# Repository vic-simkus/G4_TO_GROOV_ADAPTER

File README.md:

# G4 TO GROOV ADAPTER
## Motivation
I found out, after purchasing a pile of gear, that the G4 output modules mounted in a G4PB24 would not work with a GRV-ODCSRC-24.  Reason being that the GRV-ODCSRC-24 is a "sourcing" module, while the G4PB24 expects a "sinking" module.  

While this could have been better documented by OPTO 22, it is what is it and I needed to be able to used the G4PB24 for my project.  Nothing else would do for various reasons.

Hence this project.  The project is an adapter board with a 50 pin ribbon connector on one end and a spring loaded terminal on the other end.  The design is super simple - it's 24 NPN transistors.

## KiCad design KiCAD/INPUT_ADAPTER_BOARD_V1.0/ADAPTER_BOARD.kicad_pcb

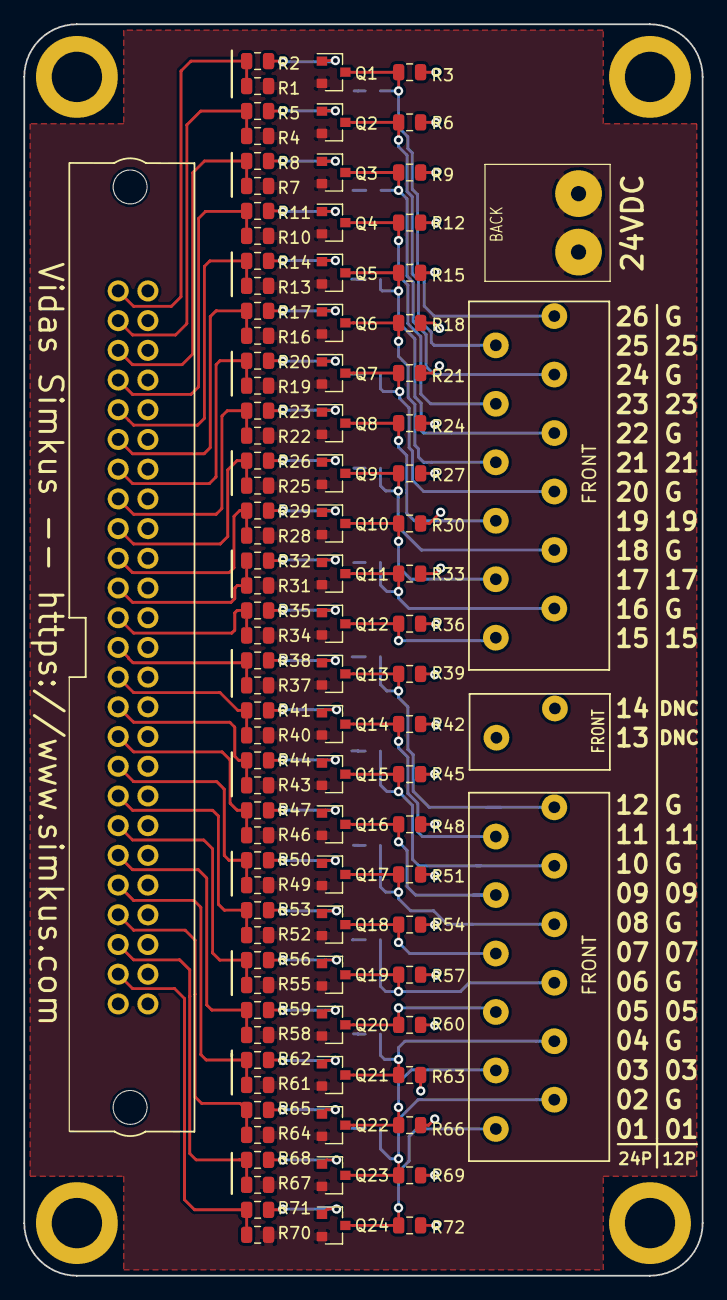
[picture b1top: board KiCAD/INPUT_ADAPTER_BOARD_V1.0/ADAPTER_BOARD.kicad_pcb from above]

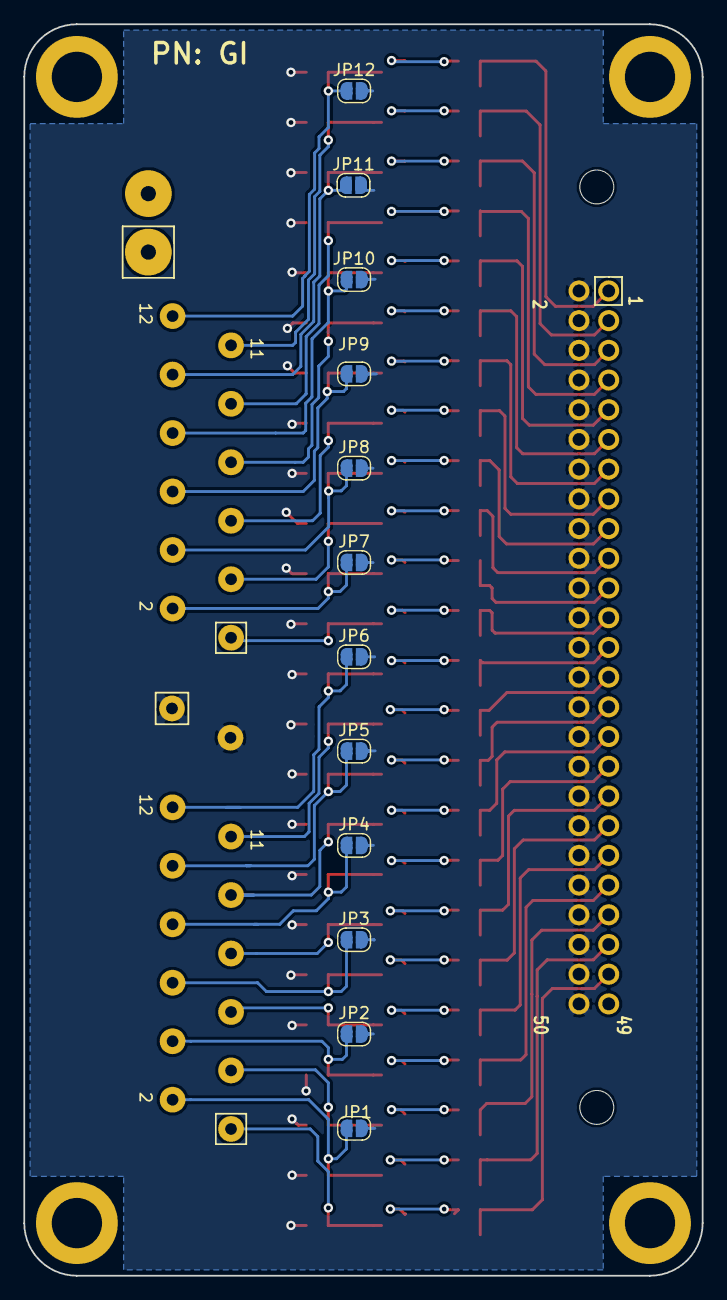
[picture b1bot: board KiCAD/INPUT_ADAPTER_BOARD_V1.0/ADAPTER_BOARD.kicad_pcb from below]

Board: 2 copper layers, 58.0 x 107.0 mm, 113 parts (12 on the bottom side), 74 nets.

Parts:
BOARD1: Conn_02x25_Odd_Even; FCI_50PIN
JP1, JP2, JP3, JP4, JP5, JP6, JP7, JP8, JP9, JP10, JP11, JP12: 12P; SolderJumper-2_P1.3mm_Open_RoundedPad1.0x1.5mm
PLC1: Conn_01x02; 2_POS_SPRING_TERM
PLC1-2, PLC13-2: Conn_01x12; 12_POS_SPRING_TERM
Q1, Q2, Q3, Q4, Q5, Q6, Q7, Q8, Q9, Q10, Q11, Q12, Q13, Q14, Q15, Q16, Q17, Q18, Q19, Q20, Q21, Q22, Q23, Q24: Q_NPN_CBE; SOT-23
R1, R2, R3, R4, R5, R6, R7, R8, R9, R10, R11, R12, R13, R14, R15, R16, R17, R18, R19, R20, R21, R22, R23, R24, R25, R26, R27, R28, R29, R30, R31, R32, R33, R34, R35, R36, R37, R38, R39, R40, R41, R42, R43, R44, R45, R46, R47, R48, R49, R50, R51, R52, R53, R54, R55, R56, R57, R58, R59, R60, R61, R62, R63, R64, R65, R66, R67, R68, R69, R70, R71, R72: 10K; R_0805_2012Metric
VDC1: Conn_01x02; 2_POS_SCREW_TERM

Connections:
24VDC: Q1.2, Q2.2, Q3.2, Q4.2, Q5.2, Q6.2, Q7.2, Q8.2, Q9.2, Q10.2, Q11.2, Q12.2, Q13.2, Q14.2, Q15.2, Q16.2, Q17.2, Q18.2, Q19.2, Q20.2, Q21.2, Q22.2, Q23.2, Q24.2, R1.2, R4.2, R7.2, R10.2, R13.2, R16.2, R19.2, R22.2, R25.2, R28.2, R31.2, R34.2, R37.2, R40.2, R43.2, R46.2, R49.2, R52.2, R55.2, R58.2, R61.2, R64.2, R67.2, R70.2, VDC1.1, VDC1.2
/B01: BOARD1.1, R1.1, R2.2
/B02: BOARD1.3, R4.1, R5.2
/B03: BOARD1.5, R7.1, R8.2
/B04: BOARD1.7, R10.1, R11.2
/B05: BOARD1.9, R13.1, R14.2
/B06: BOARD1.11, R16.1, R17.2
/B07: BOARD1.13, R19.1, R20.2
/B08: BOARD1.15, R22.1, R23.2
/B09: BOARD1.17, R25.1, R26.2
/B10: BOARD1.19, R28.1, R29.2
/B11: BOARD1.21, R31.1, R32.2
/B12: BOARD1.23, R34.1, R35.2
/B13: BOARD1.25, R37.1, R38.2
/B14: BOARD1.27, R40.1, R41.2
/B15: BOARD1.29, R43.1, R44.2
/B16: BOARD1.31, R46.1, R47.2
/B17: BOARD1.33, R49.1, R50.2
/B18: BOARD1.35, R52.1, R53.2
/B19: BOARD1.37, R55.1, R56.2
/B20: BOARD1.39, R58.1, R59.2
/B21: BOARD1.41, R61.1, R62.2
/B22: BOARD1.43, R64.1, R65.2
/B23: BOARD1.45, R67.1, R68.2
/B24: BOARD1.47, R70.1, R71.2
/P01: JP12.1, PLC1-2.12, Q1.3, R3.2
/P02: PLC1-2.11, Q2.3, R6.2
/P03: JP11.1, PLC1-2.10, Q3.3, R9.2
/P04: PLC1-2.9, Q4.3, R12.2
/P05: JP10.1, PLC1-2.8, Q5.3, R15.2
/P06: PLC1-2.7, Q6.3, R18.2
/P07: JP9.1, PLC1-2.6, Q7.3, R21.2
/P08: PLC1-2.5, Q8.3, R24.2
/P09: JP8.1, PLC1-2.4, Q9.3, R27.2
/P10: PLC1-2.3, Q10.3, R30.2
/P11: JP7.1, PLC1-2.2, Q11.3, R33.2
/P12: PLC1-2.1, Q12.3, R36.2
/P13: JP6.1, PLC13-2.12, Q13.3, R39.2
/P14: PLC13-2.11, Q14.3, R42.2
/P15: JP5.1, PLC13-2.10, Q15.3, R45.2
/P16: PLC13-2.9, Q16.3, R48.2
/P17: JP4.1, PLC13-2.8, Q17.3, R51.2
/P18: PLC13-2.7, Q18.3, R54.2
/P19: JP3.1, PLC13-2.6, Q19.3, R57.2
/P20: PLC13-2.5, Q20.3, R60.2
/P21: JP2.1, PLC13-2.4, Q21.3, R63.2
/P22: PLC13-2.3, Q22.3, R66.2
/P23: JP1.1, PLC13-2.2, Q23.3, R69.2
/P24: PLC13-2.1, Q24.3, R72.2
GND: BOARD1.2, BOARD1.4, BOARD1.6, BOARD1.8, BOARD1.10, BOARD1.12, BOARD1.14, BOARD1.16, BOARD1.18, BOARD1.20, BOARD1.22, BOARD1.24, BOARD1.26, BOARD1.28, BOARD1.30, BOARD1.32, BOARD1.34, BOARD1.36, BOARD1.38, BOARD1.40, BOARD1.42, BOARD1.44, BOARD1.46, BOARD1.48, BOARD1.50, JP1.2, JP2.2, JP3.2, JP4.2, JP5.2, JP6.2, JP7.2, JP8.2, JP9.2, JP10.2, JP11.2, JP12.2, PLC1.1, PLC1.2, R3.1, R6.1, R9.1, R12.1, R15.1, R18.1, R21.1, R24.1, R27.1, R30.1, R33.1, R36.1, R39.1, R42.1, R45.1, R48.1, R51.1, R54.1, R57.1, R60.1, R63.1, R66.1, R69.1, R72.1
unnamed: Q1.1, R2.1
unnamed: Q2.1, R5.1
unnamed: Q3.1, R8.1
unnamed: Q4.1, R11.1
unnamed: Q5.1, R14.1
unnamed: Q6.1, R17.1
unnamed: Q7.1, R20.1
unnamed: Q8.1, R23.1
unnamed: Q9.1, R26.1
unnamed: Q10.1, R29.1
unnamed: Q11.1, R32.1
unnamed: Q12.1, R35.1
unnamed: Q13.1, R38.1
unnamed: Q14.1, R41.1
unnamed: Q15.1, R44.1
unnamed: Q16.1, R47.1
unnamed: Q17.1, R50.1
unnamed: Q18.1, R53.1
unnamed: Q19.1, R56.1
unnamed: Q20.1, R59.1
unnamed: Q21.1, R62.1
unnamed: Q22.1, R65.1
unnamed: Q23.1, R68.1
unnamed: Q24.1, R71.1

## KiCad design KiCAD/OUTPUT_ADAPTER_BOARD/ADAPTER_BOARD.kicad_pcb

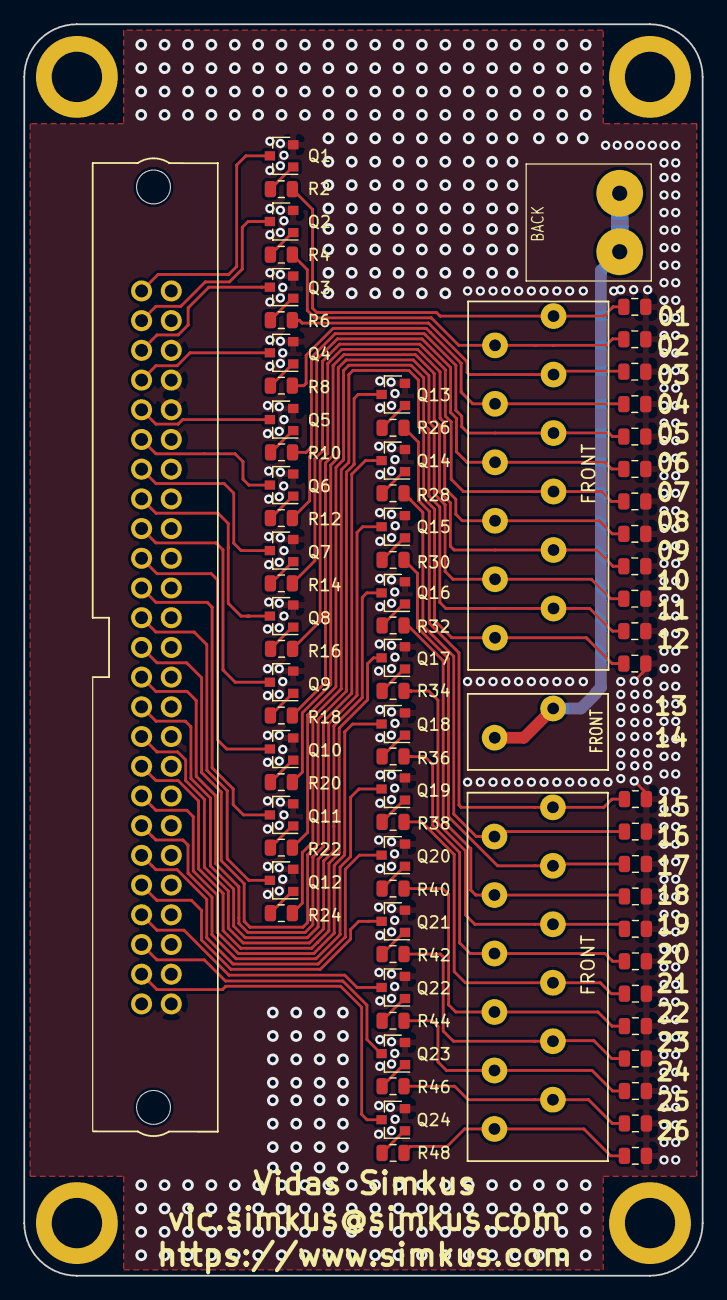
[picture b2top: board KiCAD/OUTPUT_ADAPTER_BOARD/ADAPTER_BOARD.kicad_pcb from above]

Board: 2 copper layers, 58.0 x 107.0 mm, 77 parts (0 on the bottom side), 74 nets.

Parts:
BOARD1: Conn_02x25_Odd_Even; FCI_50PIN
PLC1-12, PLC13-14: Conn_01x12; 12_POS_SPRING_TERM
PLC24: Conn_01x02; 2_POS_SPRING_TERM
Q1, Q2, Q3, Q4, Q5, Q6, Q7, Q8, Q9, Q10, Q11, Q12, Q13, Q14, Q15, Q16, Q17, Q18, Q19, Q20, Q21, Q22, Q23, Q24: Q_NPN_CBE; SOT-23
R1, R3, R5, R7, R9, R11, R13, R15, R17, R19, R21, R23, R25, R27, R29, R31, R33, R35, R37, R39, R41, R43, R45, R47: 10K; R_0805_2012Metric
R2, R4, R6, R8, R10, R12, R14, R16, R18, R20, R22, R24, R26, R28, R30, R32, R34, R36, R38, R40, R42, R44, R46, R48: 2K2; R_0805_2012Metric
VDC24: Conn_01x02; 2_POS_SCREW_TERM

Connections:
/24V: PLC24.1, PLC24.2, VDC24.1, VDC24.2
/B01: BOARD1.1, Q1.3
/B02: BOARD1.3, Q2.3
/B03: BOARD1.5, Q3.3
/B04: BOARD1.7, Q4.3
/B05: BOARD1.9, Q5.3
/B06: BOARD1.11, Q6.3
/B07: BOARD1.13, Q7.3
/B08: BOARD1.15, Q8.3
/B09: BOARD1.17, Q9.3
/B10: BOARD1.19, Q10.3
/B11: BOARD1.21, Q11.3
/B12: BOARD1.23, Q12.3
/B13: BOARD1.25, Q13.3
/B14: BOARD1.27, Q14.3
/B15: BOARD1.29, Q15.3
/B16: BOARD1.31, Q16.3
/B17: BOARD1.33, Q17.3
/B18: BOARD1.35, Q18.3
/B19: BOARD1.37, Q19.3
/B20: BOARD1.39, Q20.3
/B21: BOARD1.41, Q21.3
/B22: BOARD1.43, Q22.3
/B23: BOARD1.45, Q23.3
/B24: BOARD1.47, Q24.3
/P01: PLC1-12.12, R1.1, R2.2
/P02: PLC1-12.11, R3.1, R4.2
/P03: PLC1-12.10, R5.1, R6.2
/P04: PLC1-12.9, R7.1, R8.2
/P05: PLC1-12.8, R9.1, R10.2
/P06: PLC1-12.7, R11.1, R12.2
/P07: PLC1-12.6, R13.1, R14.2
/P08: PLC1-12.5, R15.1, R16.2
/P09: PLC1-12.4, R17.1, R18.2
/P10: PLC1-12.3, R19.1, R20.2
/P11: PLC1-12.2, R21.1, R22.2
/P12: PLC1-12.1, R23.1, R24.2
/P13: PLC13-14.12, R25.1, R26.2
/P14: PLC13-14.11, R27.1, R28.2
/P15: PLC13-14.10, R29.1, R30.2
/P16: PLC13-14.9, R31.1, R32.2
/P17: PLC13-14.8, R33.1, R34.2
/P18: PLC13-14.7, R35.1, R36.2
/P19: PLC13-14.6, R37.1, R38.2
/P20: PLC13-14.5, R39.1, R40.2
/P21: PLC13-14.4, R41.1, R42.2
/P22: PLC13-14.3, R43.1, R44.2
/P23: PLC13-14.2, R45.1, R46.2
/P24: PLC13-14.1, R47.1, R48.2
GND: BOARD1.2, BOARD1.4, BOARD1.6, BOARD1.8, BOARD1.10, BOARD1.12, BOARD1.14, BOARD1.16, BOARD1.18, BOARD1.20, BOARD1.22, BOARD1.24, BOARD1.26, BOARD1.28, BOARD1.30, BOARD1.32, BOARD1.34, BOARD1.36, BOARD1.38, BOARD1.40, BOARD1.42, BOARD1.44, BOARD1.46, BOARD1.48, BOARD1.50, Q1.2, Q2.2, Q3.2, Q4.2, Q5.2, Q6.2, Q7.2, Q8.2, Q9.2, Q10.2, Q11.2, Q12.2, Q13.2, Q14.2, Q15.2, Q16.2, Q17.2, Q18.2, Q19.2, Q20.2, Q21.2, Q22.2, Q23.2, Q24.2, R1.2, R3.2, R5.2, R7.2, R9.2, R11.2, R13.2, R15.2, R17.2, R19.2, R21.2, R23.2, R25.2, R27.2, R29.2, R31.2, R33.2, R35.2, R37.2, R39.2, R41.2, R43.2, R45.2, R47.2
unnamed: Q1.1, R2.1
unnamed: Q2.1, R4.1
unnamed: Q3.1, R6.1
unnamed: Q4.1, R8.1
unnamed: Q5.1, R10.1
unnamed: Q6.1, R12.1
unnamed: Q7.1, R14.1
unnamed: Q8.1, R16.1
unnamed: Q9.1, R18.1
unnamed: Q10.1, R20.1
unnamed: Q11.1, R22.1
unnamed: Q12.1, R24.1
unnamed: Q13.1, R26.1
unnamed: Q14.1, R28.1
unnamed: Q15.1, R30.1
unnamed: Q16.1, R32.1
unnamed: Q17.1, R34.1
unnamed: Q18.1, R36.1
unnamed: Q19.1, R38.1
unnamed: Q20.1, R40.1
unnamed: Q21.1, R42.1
unnamed: Q22.1, R44.1
unnamed: Q23.1, R46.1
unnamed: Q24.1, R48.1

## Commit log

2019-05-30 Initial import.
2019-05-30 Added board screen shot
2019-05-30 Update README.md
    Added screen shot of board.
2019-06-11 Added DXF files.
2019-06-11 Moved around directory structure
2019-06-11 Text label updates.
2019-06-12 V2 of the board.
2019-06-12 Created copy of output board V1.1 stuff as it was sent to fab.
2019-06-13 Started working on the input adapter.
2019-06-13 Added readme to datasheets directory.
2019-06-19 Finalized and shipped the input adapter board V1.0 to production.
2019-06-19 Archived V1.0 that was sent to production.
2019-06-19 Footprint updates.
2019-08-17 Removed temp file.
2019-08-17 Updated BOM files.
2019-08-17 Added PDF export of BOM file.
2020-01-26 Added missing file
